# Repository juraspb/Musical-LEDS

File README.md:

# Musical-LEDS

This is a project for self-assembly of the LED strip color music controller.

One of the main features of such controller is that you can easily make it out of cheap and accessible modules, which you may find in popular online stores.
The controller supports LED strips of from 30 to 240 diodes. Before use, you should set the number of diodes in your strip by pressing the LED button. Then save the set value to NVRAM by pressing the SAVE button.
Presented software allows you to enjoy more than 10 built-in musical programs and over 44 dynamical programs. Taking into account all the variations of motion and colors, you will find that overall number of programs exceeds 1000! You can simply choose any program, set up direction of motion, LED strip brightness, motion speed, and comfortable white light color temperature. Moreover, we will continuously release new musical and dynamical programs!
The controller also allows you to make a playlist of dynamical programs. Just add any dynamical program you like to playlist by pressing the ADD button. Using this feature, you can create the playlist of dynamical programs that will alternate each other in order you want with unique motion speed for every program. To clear playlist hold the ADD button for more than 5 seconds. Check the box labeled playlist to start the cyclic playing. Do not forget to save your playlist to NVRAM by pressing the SAVE button.
Using the buttons OFF and CBET, you may turn the LED strip off or turn on simple white lighting at any time.
You may set up your controller from any terminal software using AT commands. To get the command list, use the AT+H command. You can also set colors of the dynamical programs from terminal.
Everything needed to start your amazing LED strip musical experience is to install our firmware on the STM32F103 microcontroller. Assembly instructions and firmware are available to download from the developer’s web site and from the Musical LEDs Facebook group.
Have a nice time!

Video of this controller is presented on YouTube:

https://www.youtube.com/watch?v=DBuPlFtg0Nw

https://www.youtube.com/watch?v=5vanh8qdEC8

https://www.youtube.com/watch?v=MFy6SZ60tzc

1. Download the firmware to the microcontroller.
2. Collect the scheme.
3. Connect the LED strip and power supply.
4. Turn on the power.
5. Set the number of LEDs in the strip. Use the button B9 for this or connect from the PC to the USB port and use the AT commands from any terminal program to configure.
6. Select the desired program and parameters using the buttons or the application for Android.

Enjoy your holiday.

The program for Android is available for download on Google Play:

https://play.google.com/store/apps/details?id=ru.juraspb.cmu.bluetoothchat

Welcome to this project group:

https://www.facebook.com/groups/336136297134996/

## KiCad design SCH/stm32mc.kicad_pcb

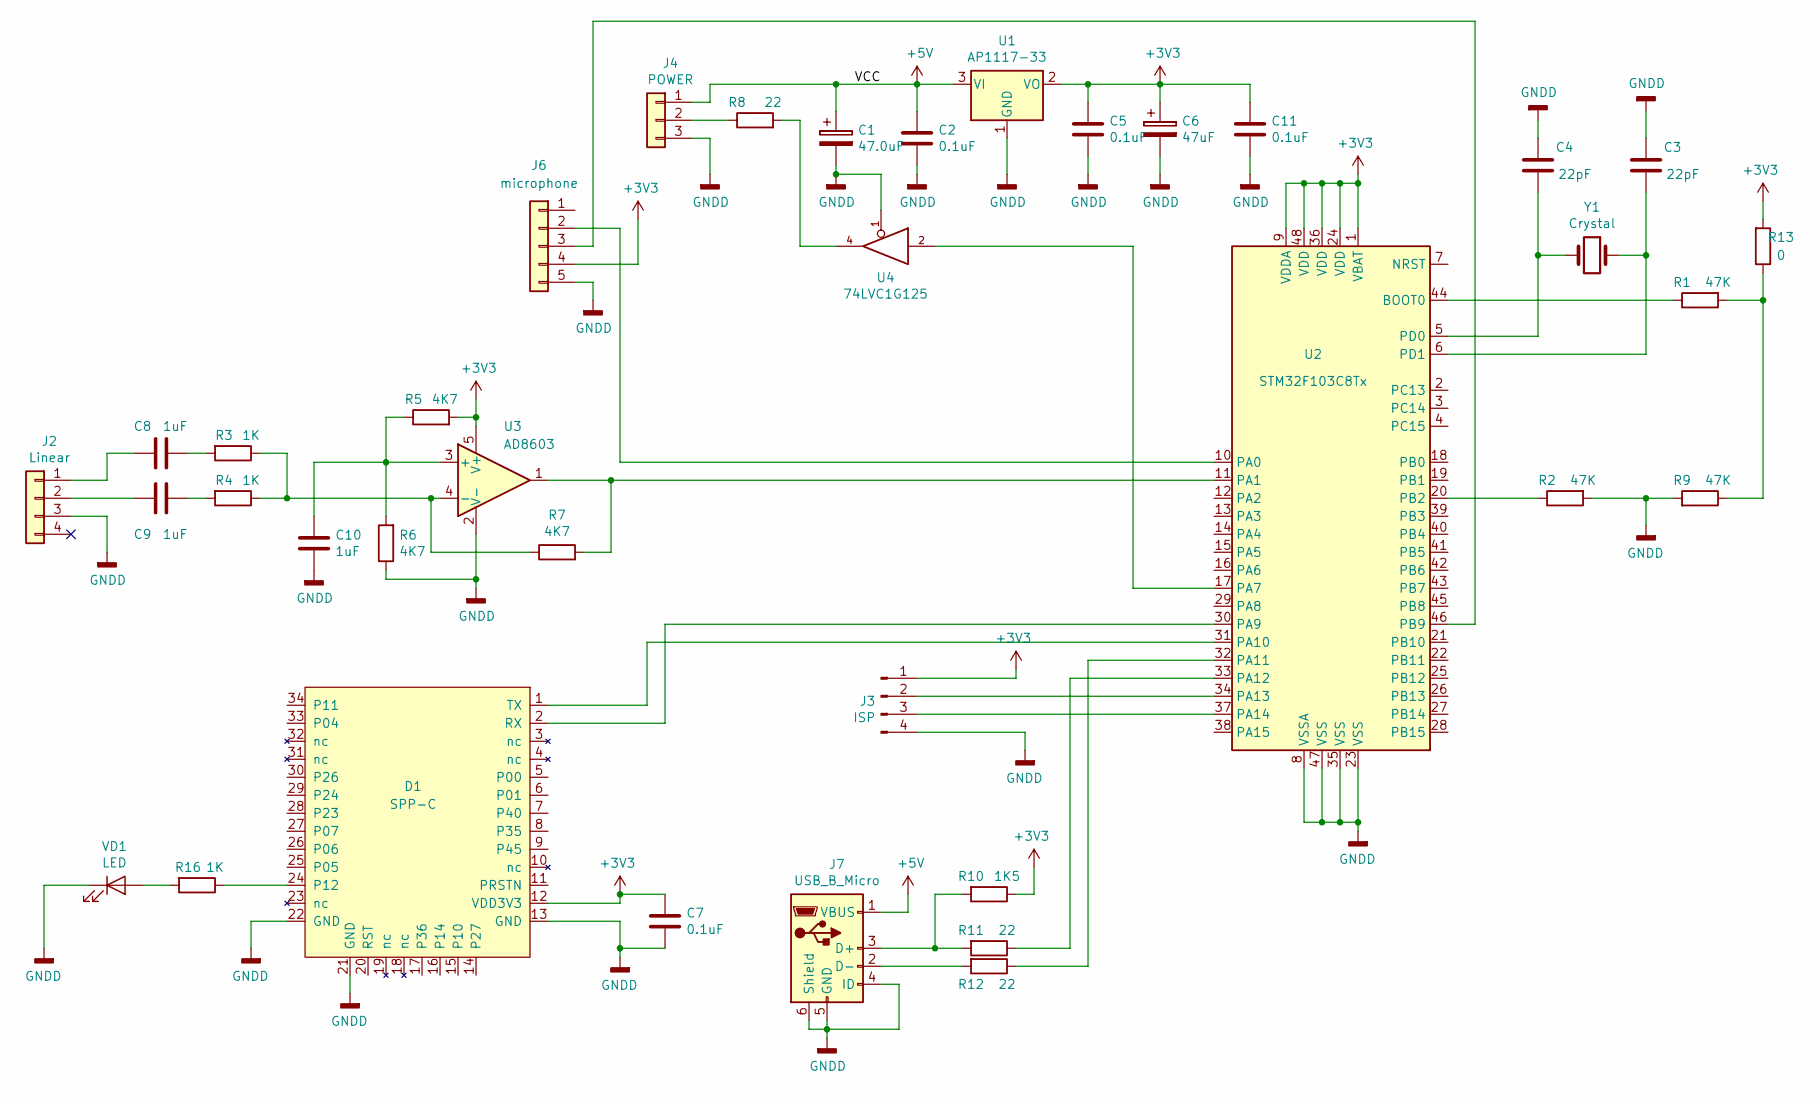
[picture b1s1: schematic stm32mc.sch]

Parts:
C1: 47.0uF; C_1210_3225Metric
C2, C5, C7, C11: 0.1uF; C_0603_1608Metric
C3, C4: 22pF; C_0603_1608Metric
C6: 47uF; C_1210_3225Metric
C8, C9, C10: 1uF; C_0603_1608Metric
D1: SPP-C; SPP-C_cmu
J2: Linear; Jack_3.5mm_PJ320D_Horizontal
J3: ISP; Molex_PicoBlade_53261-0471_1x04-1MP_P1.25mm_Horizontal
J4: POWER; PhoenixContact_MC_1,5_3-G-3.81_1x03_P3.81mm_Horizontal
J6: microphone; PinHeader_1x05_P2.54mm_Vertical
J7: USB_B_Micro; USB_Micro-B_Molex_47346-0001
R1, R2, R9: 47K; R_0603_1608Metric
R3, R4, R16: 1K; R_0603_1608Metric
R5, R6, R7: 4K7; R_0603_1608Metric
R8, R11, R12: 22; R_0603_1608Metric
R10: 1K5; R_0603_1608Metric
R13: 0; R_0603_1608Metric
U1: AP1117-33; SOT-223-3_TabPin2
U2: STM32F103C8Tx; LQFP-48_7x7mm_P0.5mm
U3: AD8603; TSOT-23-5
U4: 74LVC1G125; SOT-23-5_HandSoldering
VD1: LED; LED_0603_1608Metric
Y1: Crystal; Crystal_SMD_5032-2Pin_5.0x3.2mm

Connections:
+3V3: C5.1, C6.1, C7.1, C11.1, D1.12 (VDD3V3), J3.1, J6.4, R5.2, R10.1, R13.2, U1.2 (VO), U2.1 (VBAT), U2.9 (VDDA), U2.24 (VDD), U2.36 (VDD), U2.48 (VDD), U3.5 (V+)
+5V: C1.1, C2.1, J4.1, J7.1 (VBUS), U1.3 (VI), U4.5 (VCC)
GND: U4.3 (GND)
GNDD: C1.2, C2.2, C3.1, C4.1, C5.2, C6.2, C7.2, C10.2, C11.2, D1.13 (GND), D1.21 (GND), D1.22 (GND), J2.3, J3.4, J4.3, J6.5, J7.4 (ID), J7.5 (GND), J7.6 (Shield), R2.2, R6.1, R9.2, U1.1 (GND), U2.8 (VSSA), U2.23 (VSS), U2.35 (VSS), U2.47 (VSS), U3.2 (V-), U4.1, VD1.1 (K)
unnamed: C3.2, U2.6 (PD1), Y1.1
unnamed: C4.2, U2.5 (PD0), Y1.2
unnamed: C8.1, J2.1
unnamed: C8.2, R3.2
unnamed: C9.1, J2.2
unnamed: C9.2, R4.2
unnamed: C10.1, R5.1, R6.2, U3.3 (+)
unnamed: D1.1 (TX), U2.31 (PA10)
unnamed: D1.2 (RX), U2.30 (PA9)
unnamed: D1.24 (P12), R16.1
unnamed: J3.2, U2.34 (PA13)
unnamed: J3.3, U2.37 (PA14)
unnamed: J4.2, R8.1
unnamed: J6.2, U2.10 (PA0)
unnamed: J6.3, U2.46 (PB9)
unnamed: J7.2 (D-), R12.2
unnamed: J7.3 (D+), R10.2, R11.2
unnamed: R1.1, U2.44 (BOOT0)
unnamed: R1.2, R9.1, R13.1
unnamed: R2.1, U2.20 (PB2)
unnamed: R3.1, R4.1, R7.1, U3.4 (-)
unnamed: R7.2, U2.11 (PA1), U3.1
unnamed: R8.2, U4.4
unnamed: R11.1, U2.33 (PA12)
unnamed: R12.1, U2.32 (PA11)
unnamed: R16.2, VD1.2 (A)
unnamed: U2.17 (PA7), U4.2

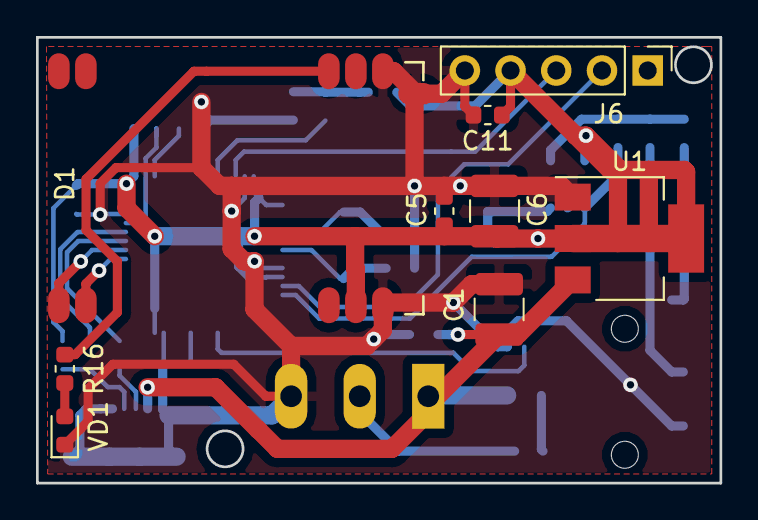
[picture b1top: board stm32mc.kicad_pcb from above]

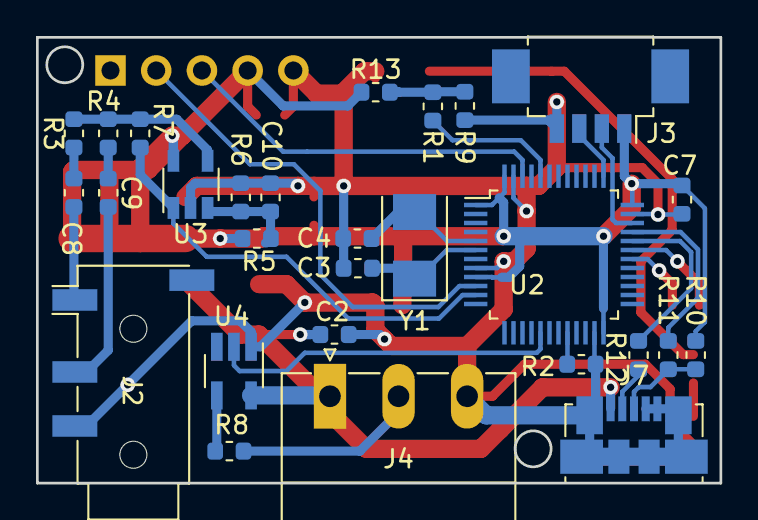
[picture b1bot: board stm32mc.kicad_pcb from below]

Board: 2 copper layers, 38.0 x 24.8 mm, 37 parts (28 on the bottom side), 30 nets.

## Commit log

2018-10-23 assembly drawing file loaded
2018-10-23 microcontroller firmware file loaded
2018-10-23 add description
2018-10-23 Create configurations
2018-10-23 Android apps
2018-10-23 Added links.
2018-11-20 new firmware
    new firmware
2018-11-20 firmware update manual
    firmware update manual
2018-11-20 user manual
2018-12-01 User manual
    User manual
2018-12-01 firmware
    firmware
2018-12-01 applications view
    applications view
2018-12-01 Musical leds
    Musical leds
2018-12-01 Create 1
2018-12-01 view
    View Musical LEDs
2018-12-01 Create 2
2018-12-01 application
    View android application
2018-12-01 firmware installation
    firmware installation
2019-12-10 Delete MC.hex
    new ready
2019-12-10 Add files via upload
    new
2019-12-10 Create readme
    new
2019-12-10 Add files via upload
    new CMU control programm
2019-12-12 Add files via upload
    Schematic and PCB
